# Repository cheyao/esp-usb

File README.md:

# ESP USB - ESP32 in your pockets

## Description

The tiny ESP32 development board that you can plug directly into your USB port.

- This board is tiny - enabling small projects. Has 8 GPIO pins, allowing diverse applications.
- It is portable - no external devices (except your laptop) are needed in order to program the chip! Have one of these in your pockets allowes you to create from anywhere.
- It is routed only using 2 layers, thus lowering per unit cost.
- It has a onboard 600mA voltage regulator

You can directly plug it into your USB port and program it, using your favourite IDE.

Features:
- Small 30x18mm footprint
- Portable - Plus & play
- Reliable - EING surface finish
- PCB USB receptacle - No cables needed
- 8 GPIOs - Do anything you want
- 2 user leds - Easy debugging
- Breadboard pinout

## Notes

If you need to supply 5v, solder a wire onto the usb pad.

This board needs to be 2.0mm thick in order to be sticked into a USB port.

### License

Licensed under Solderpad license, basically you can do anything but the board doesn't come with guarantee.

## This is not suited for production yet

I need to add some more decoupling caps & do more verification on the antenna

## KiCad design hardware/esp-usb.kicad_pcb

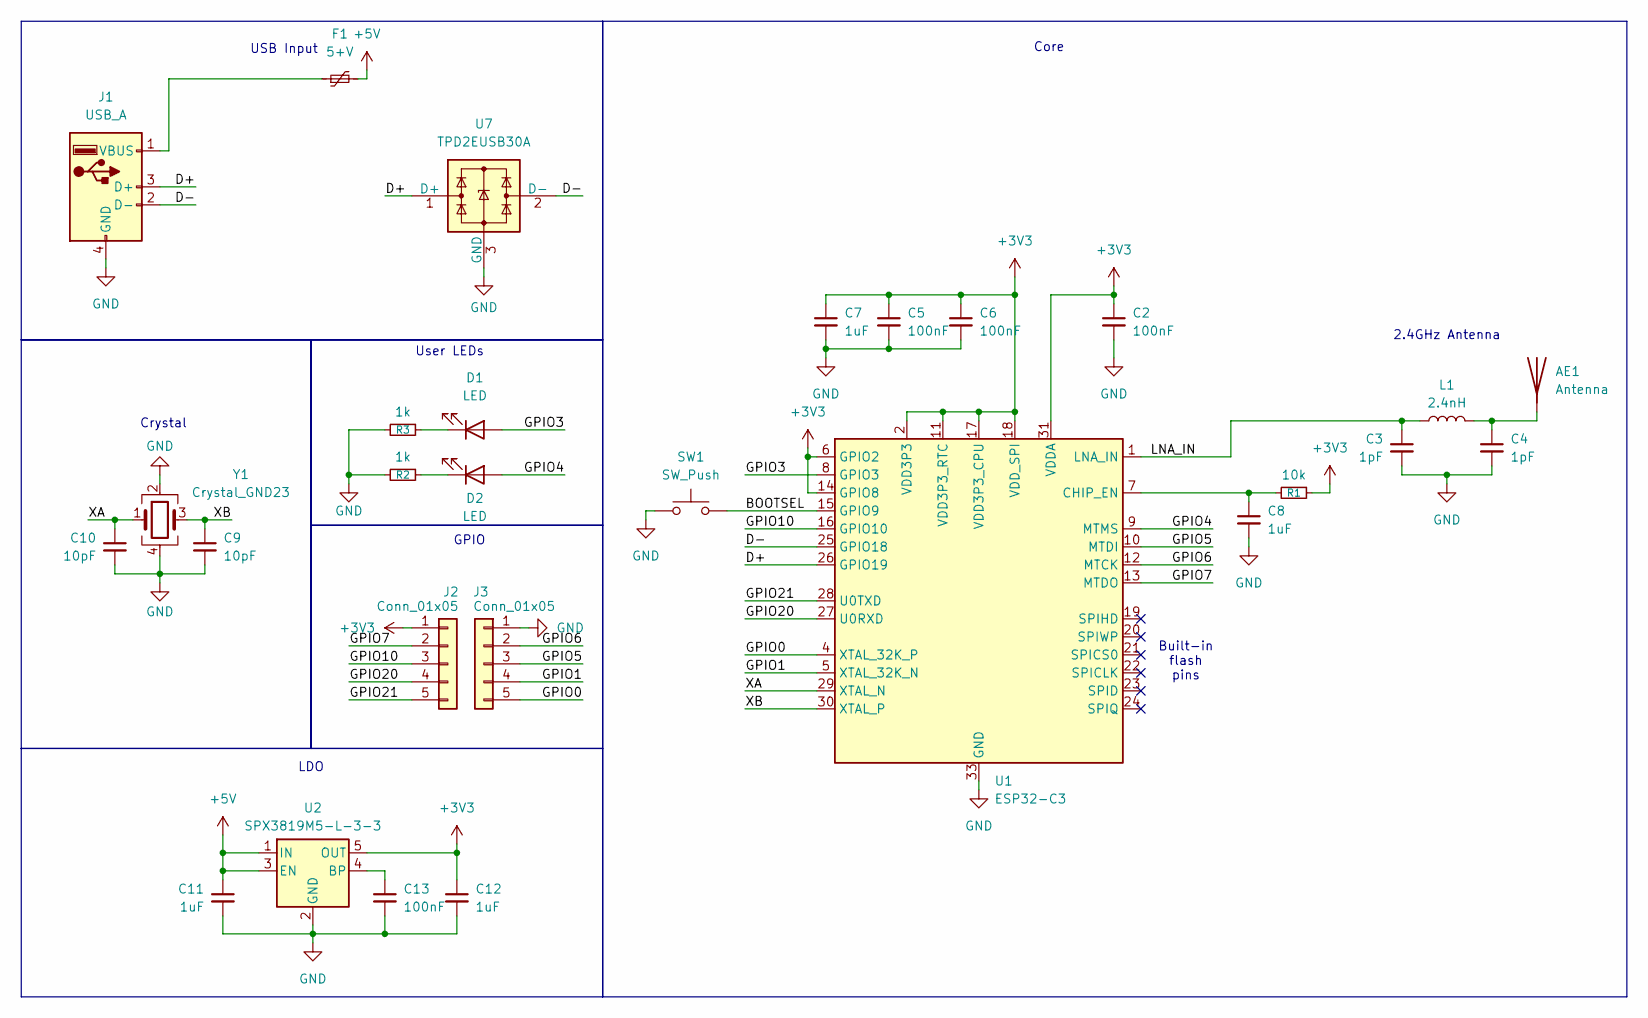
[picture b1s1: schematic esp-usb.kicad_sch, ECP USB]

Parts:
AE1: Antenna; Johanson_2450AT18x100; LCSC Part # C127629
C2, C5, C6, C13: 100nF; C_0402_1005Metric; LCSC Part # C1525
C3, C4: 1pF; C_0402_1005Metric; LCSC Part # C1550
C7, C8, C11, C12: 1uF; C_0402_1005Metric; LCSC Part # C52923
C9, C10: 10pF; C_0402_1005Metric; LCSC Part # C32949
D1, D2: LED; LED_0603_1608Metric; LCSC Part # C2290
F1: 5+V; Fuse_0603_1608Metric; LCSC Part # C70046
J1: USB_A; USBPCB
J2, J3: Conn_01x05; PinHeader_1x05_P2.54mm_Vertical
L1: 2.4nH; L_0402_1005Metric; LCSC Part # C142237
R1: 10k; R_0402_1005Metric; LCSC Part # C25744
R2, R3: 1k; R_0402_1005Metric; LCSC Part # C11702
SW1: SW_Push; SW_SPST_B3U-1000P; LCSC Part # C2764561
U1: ESP32-C3; QFN-32-1EP_5x5mm_P0.5mm_EP3.7x3.7mm; LCSC Part # C2858491
U2: SPX3819M5-L-3-3; SOT-23-5; LCSC Part # C9055
U7: TPD2EUSB30A; Texas_DRT-3; LCSC Part # C3011197
Y1: Crystal_GND23; Crystal_SMD_2016-4Pin_2.0x1.6mm; LCSC Part # C424432

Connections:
+3V3: C2.1, C5.1, C6.1, C7.1, C12.1, J2.1, R1.1, U1.2 (VDD3P3), U1.3 (VDD3P3), U1.6 (GPIO2), U1.11 (VDD3P3_RTC), U1.14 (GPIO8), U1.17 (VDD3P3_CPU), U1.18 (VDD_SPI), U1.31 (VDDA), U1.32 (VDDA), U2.5 (OUT)
+5V: C11.1, F1.2, U2.1 (IN), U2.3 (EN)
/BOOTSEL: SW1.1, U1.15 (GPIO9)
/D+: J1.3 (D+), U1.26 (GPIO19), U7.1 (D+)
/D-: J1.2 (D-), U1.25 (GPIO18), U7.2 (D-)
/GPIO0: J3.5, U1.4 (XTAL_32K_P)
/GPIO1: J3.4, U1.5 (XTAL_32K_N)
/GPIO3: D1.2 (A), U1.8 (GPIO3)
/GPIO4: D2.2 (A), U1.9 (MTMS)
/GPIO5: J3.3, U1.10 (MTDI)
/GPIO6: J3.2, U1.12 (MTCK)
/GPIO7: J2.2, U1.13 (MTDO)
/GPIO10: J2.3, U1.16 (GPIO10)
/GPIO20: J2.4, U1.27 (U0RXD)
/GPIO21: J2.5, U1.28 (U0TXD)
/LNA_IN: C3.1, L1.1, U1.1 (LNA_IN)
/XA: C10.1, U1.29 (XTAL_N), Y1.1
/XB: C9.1, U1.30 (XTAL_P), Y1.3
GND: C2.2, C3.2, C4.2, C5.2, C6.2, C7.2, C8.2, C9.2, C10.2, C11.2, C12.2, C13.2, J1.4 (GND), J3.1, R2.2, R3.2, SW1.2, U1.33 (GND), U2.2 (GND), U7.3 (GND), Y1.2, Y1.4
unnamed: AE1.1 (A), C4.1, L1.2
unnamed: D1.1 (K), R3.1
unnamed: D2.1 (K), R2.1
unnamed: F1.1, J1.1 (VBUS)
unnamed: C8.1, R1.2, U1.7 (CHIP_EN)
unnamed: C13.1, U2.4 (BP)

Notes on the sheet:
2.4GHz Antenna
Core
USB Input
User LEDs
LDO
Crystal
GPIO
Built-in flash pins

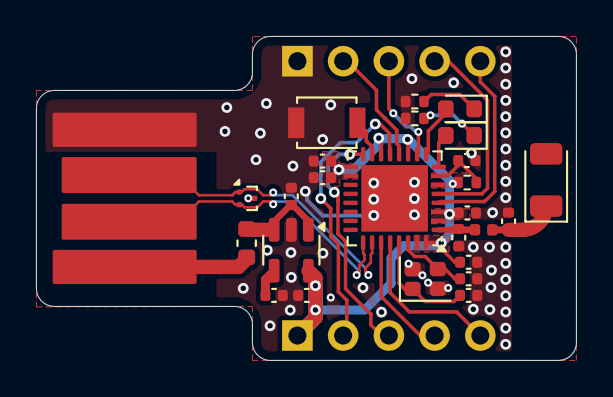
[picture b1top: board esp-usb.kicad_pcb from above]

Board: 2 copper layers, 30.0 x 18.0 mm, 28 parts (0 on the bottom side), 25 nets.

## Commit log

2025-05-17 Init
2025-05-17 Workieeee
2025-05-18 beta version!
2025-05-19 Rev 3 ig
2025-05-20 Final rev!
2025-05-21 Beautify journal
2025-05-21 Opps
2025-05-21 Titles
2025-05-21 Fixxx
2025-05-28 Expand readme
2025-07-02 Use IRL pic
2025-07-02 Remove back fill
2026-01-22 Fix broken CDN links
